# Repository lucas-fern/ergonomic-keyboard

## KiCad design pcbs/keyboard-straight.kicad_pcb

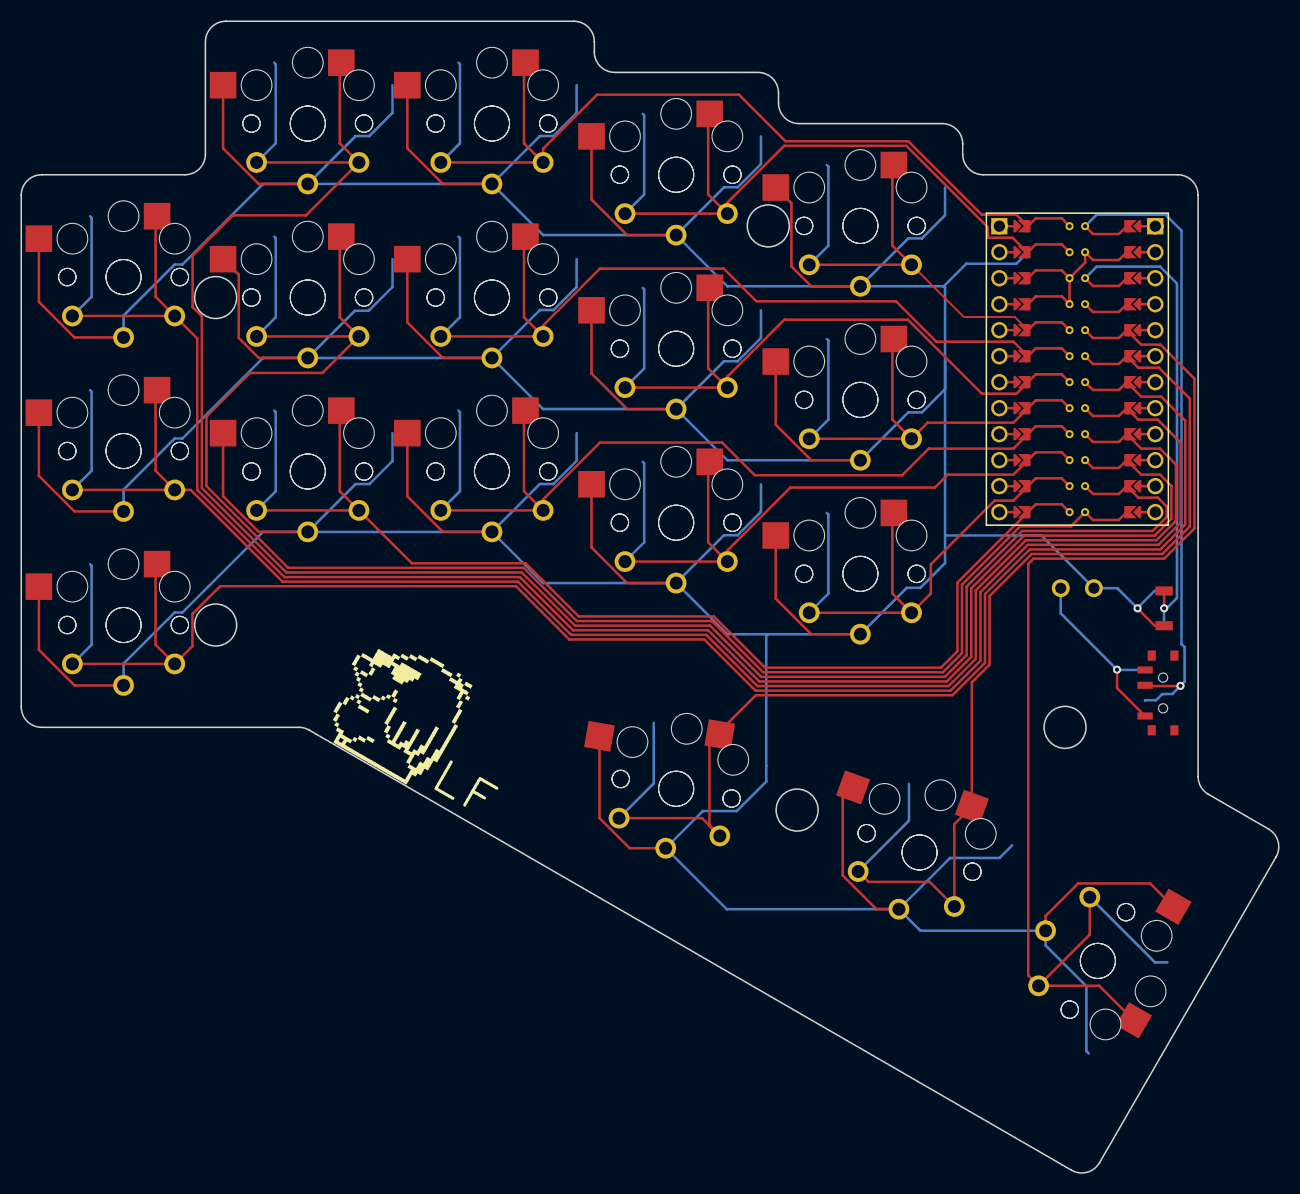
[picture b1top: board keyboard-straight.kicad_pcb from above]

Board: 2 copper layers, 122.9 x 112.5 mm, 36 parts (0 on the bottom side), 19 nets.

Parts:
S1, S2, S3, S4, S5, S6, S7, S8, S9, S10, S11, S12, S13, S14, S15, S16, S17, S18, S19, S20, S21, S22, S23, S24, S25, S26, S27, S28, S29, S30, S31, S32, S33, S34, S35, S36: PG1350

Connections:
GND: S1.2, S2.2, S3.2, S4.2, S5.2, S6.2, S7.2, S8.2, S9.2, S10.2, S11.2, S12.2, S13.2, S14.2, S15.2, S16.2, S17.2, S18.2, S19.2, S20.2, S21.2, S22.2, S23.2, S24.2, S25.2, S26.2, S27.2, S28.2, S29.2, S30.2, S31.2, S32.2, S33.2, S34.2, S35.2, S36.2
P0: S23.1, S24.1
P1: S17.1, S18.1
P2: S29.1, S30.1
P3: S15.1, S16.1
P4: S21.1, S22.1
P5: S27.1, S28.1
P6: S13.1, S14.1
P7: S19.1, S20.1
P8: S25.1, S26.1
P9: S7.1, S8.1
P10: S9.1, S10.1
P14: S5.1, S6.1
P15: S3.1, S4.1
P16: S11.1, S12.1
P18: S1.1, S2.1
P19: S31.1, S32.1
P20: S33.1, S34.1
P21: S35.1, S36.1

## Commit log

2022-02-08 fixed DRC violations on straight PCB
